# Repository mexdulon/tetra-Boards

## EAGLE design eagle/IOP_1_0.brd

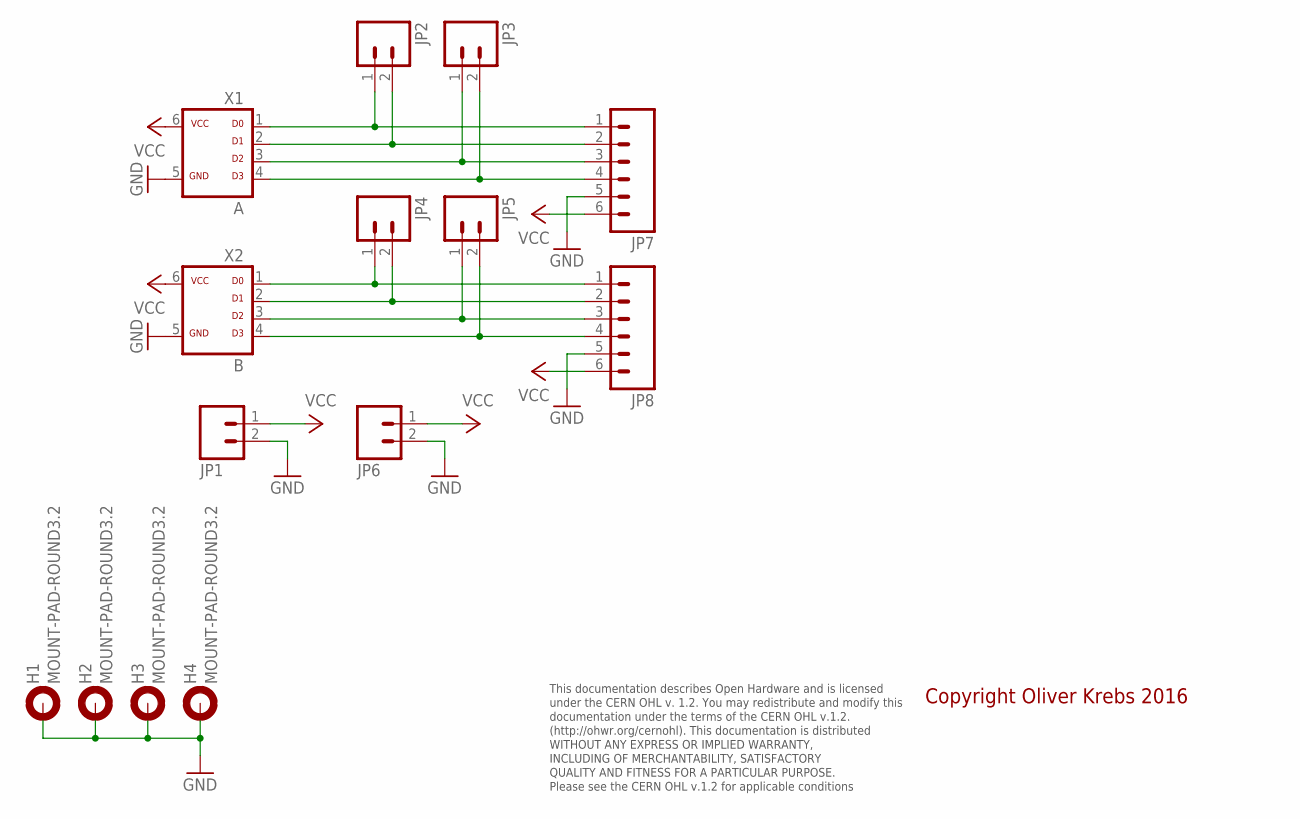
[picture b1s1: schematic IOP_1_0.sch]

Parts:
H1, H2, H3, H4: MOUNT-PAD-ROUND3.2; 3,2-PAD
JP1, JP2, JP3, JP4, JP5, JP6: M021.3MM-5.08; 1X02_BIG_5.08
JP7, JP8: M06SILK_FEMALE_PTH; 1X06
X1: A; ML-6
X2: B; ML-6

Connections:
GND: H1.B3,2, H2.B3,2, H3.B3,2, H4.B3,2, JP1.2, JP6.2, JP7.5, JP8.5, X1.5, X2.5
unnamed: JP2.2, JP7.2, X1.2
unnamed: JP2.1, JP7.1, X1.1
unnamed: JP3.1, JP7.3, X1.3
unnamed: JP3.2, JP7.4, X1.4
unnamed: JP4.1, JP8.1, X2.1
unnamed: JP4.2, JP8.2, X2.2
unnamed: JP5.1, JP8.3, X2.3
unnamed: JP5.2, JP8.4, X2.4
VCC: JP1.1, JP6.1, JP7.6, JP8.6, X1.6, X2.6

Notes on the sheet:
This documentation describes Open Hardware and is licensed under the CERN OHL v. 1.2. You may redistribute and modify this documentation under the terms of the CERN OHL v.1.2. (http://ohwr.org/cernohl). This documentation is distributed WITHOUT ANY EXPRESS OR IMPLIED WARRANTY, INCLUDING OF MERCHANT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
Copyright Oliver Krebs 2016

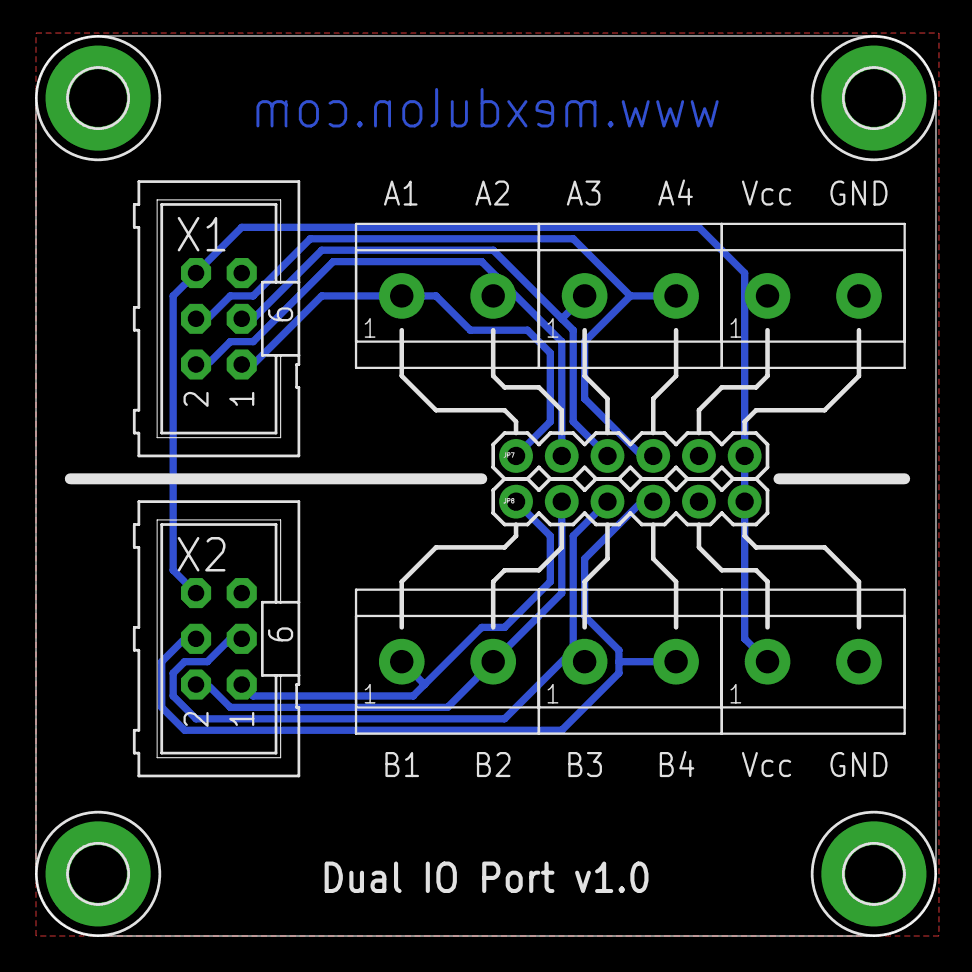
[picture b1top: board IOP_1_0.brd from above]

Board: 2 copper layers, 50.0 x 50.0 mm, 14 parts (0 on the bottom side), 10 nets.

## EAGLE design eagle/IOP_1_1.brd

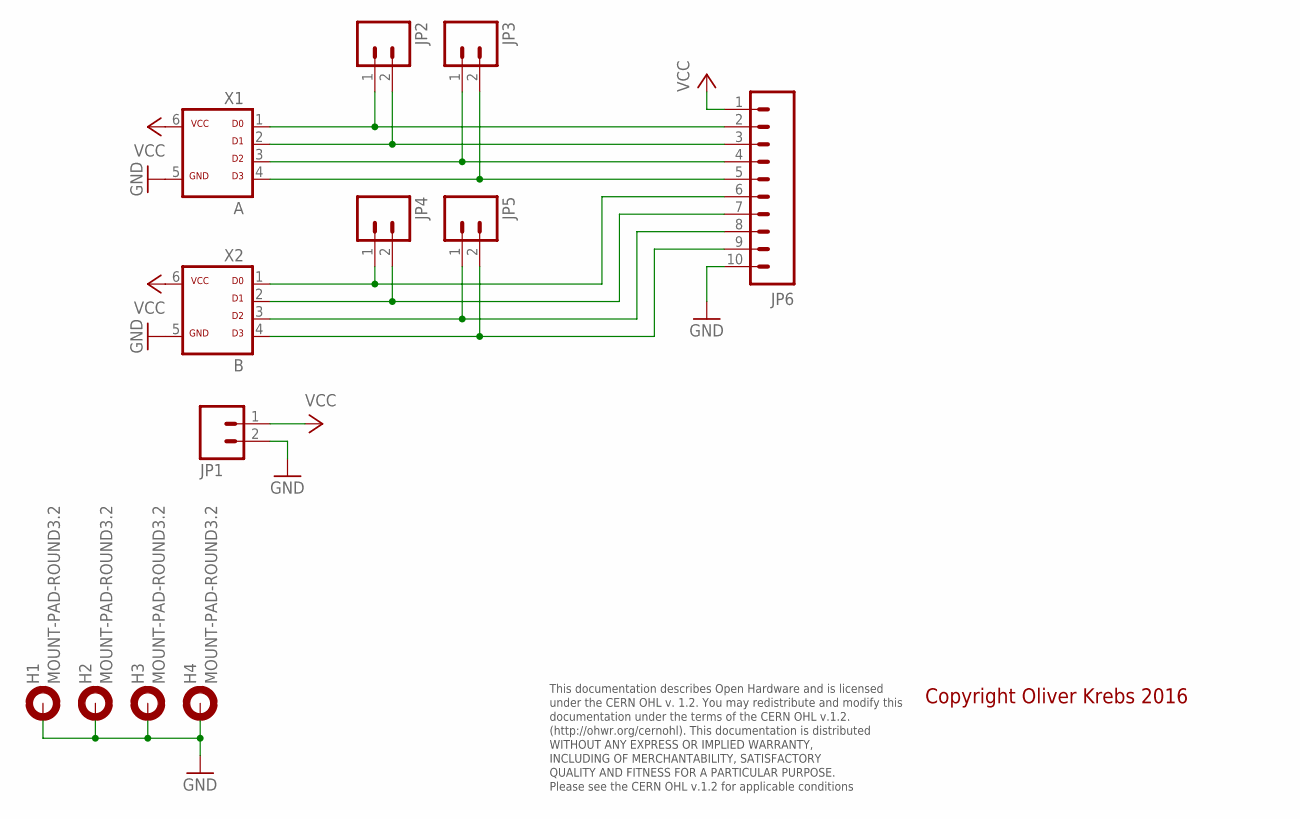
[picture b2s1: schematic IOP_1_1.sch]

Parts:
H1, H2, H3, H4: MOUNT-PAD-ROUND3.2; 3,2-PAD
JP1, JP2, JP3, JP4, JP5: M021.3MM-5.08; 1X02_BIG_5.08
JP6: M10SILK_FEMALE_PTH; 1X10
X1: A; ML-6
X2: B; ML-6

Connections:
GND: H1.B3,2, H2.B3,2, H3.B3,2, H4.B3,2, JP1.2, JP6.10, X1.5, X2.5
unnamed: JP2.2, JP6.3, X1.2
unnamed: JP2.1, JP6.2, X1.1
unnamed: JP3.1, JP6.4, X1.3
unnamed: JP3.2, JP6.5, X1.4
unnamed: JP4.1, JP6.6, X2.1
unnamed: JP4.2, JP6.7, X2.2
unnamed: JP5.1, JP6.8, X2.3
unnamed: JP5.2, JP6.9, X2.4
VCC: JP1.1, JP6.1, X1.6, X2.6

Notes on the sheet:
This documentation describes Open Hardware and is licensed under the CERN OHL v. 1.2. You may redistribute and modify this documentation under the terms of the CERN OHL v.1.2. (http://ohwr.org/cernohl). This documentation is distributed WITHOUT ANY EXPRESS OR IMPLIED WARRANTY, INCLUDING OF MERCHANT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
Copyright Oliver Krebs 2016

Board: 2 copper layers, 12 parts (0 on the bottom side), 10 nets, no tracks yet.

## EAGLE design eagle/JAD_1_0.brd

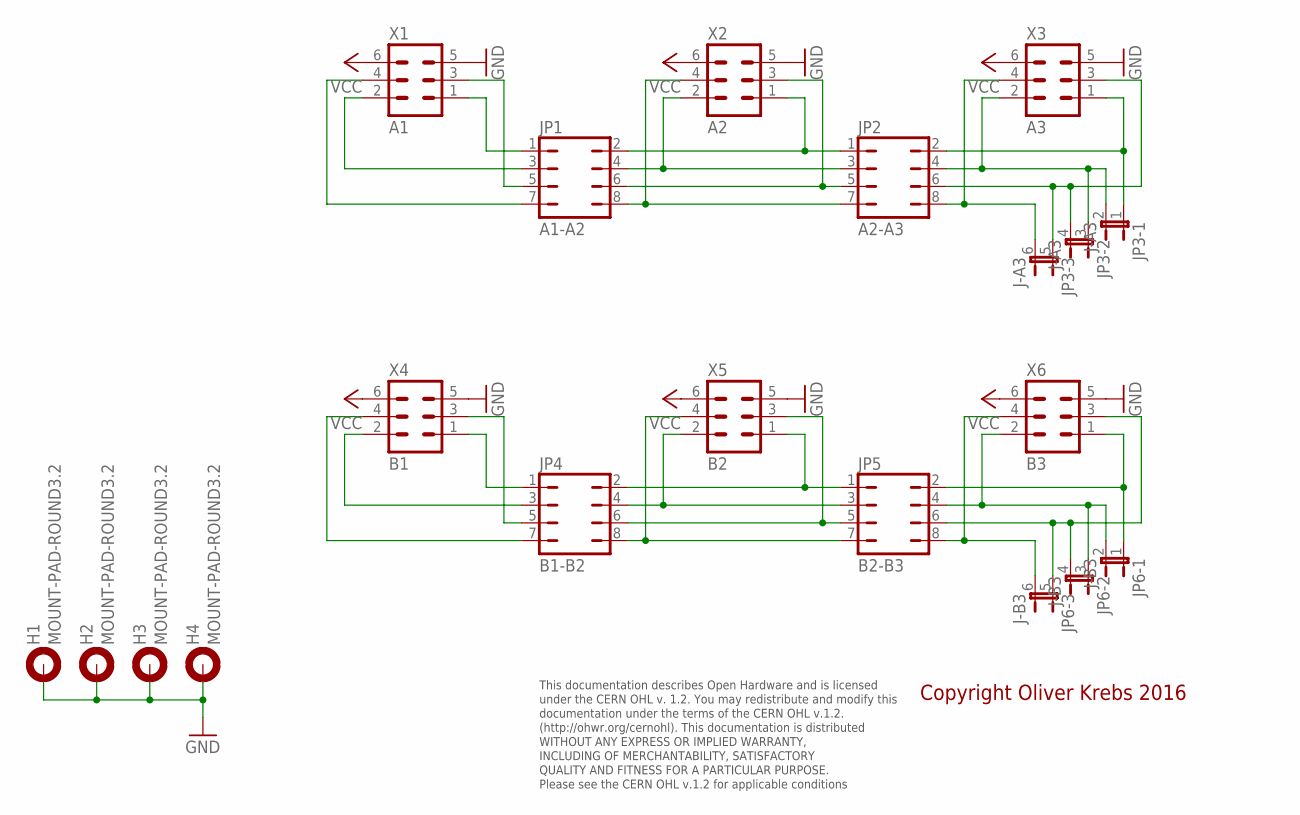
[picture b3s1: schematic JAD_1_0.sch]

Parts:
H1, H2, H3, H4: MOUNT-PAD-ROUND3.2; 3,2-PAD
JP1: A1-A2; JP4Q
JP2: A2-A3; JP4Q
JP3: J-A3; JP3Q
JP4: B1-B2; JP4Q
JP5: B2-B3; JP4Q
JP6: J-B3; JP3Q
X1: A1; ML-6
X2: A2; ML-6
X3: A3; ML-6
X4: B1; ML-6
X5: B2; ML-6
X6: B3; ML-6

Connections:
GND: H1.B3,2, H2.B3,2, H3.B3,2, H4.B3,2, X1.5, X2.5, X3.5, X4.5, X5.5, X6.5
unnamed: JP1.1, X1.1
unnamed: JP1.3, X1.2
unnamed: JP1.5, X1.3
unnamed: JP1.7, X1.4
unnamed: JP1.2, JP2.1, X2.1
unnamed: JP1.4, JP2.3, X2.2
unnamed: JP1.6, JP2.5, X2.3
unnamed: JP1.8, JP2.7, X2.4
unnamed: JP2.2, JP3.1, X3.1
unnamed: JP2.4, JP3.2, JP3.3 (1), X3.2
unnamed: JP2.6, JP3.4 (2), JP3.5 (1), X3.3
unnamed: JP2.8, JP3.6 (2), X3.4
unnamed: JP4.1, X4.1
unnamed: JP4.3, X4.2
unnamed: JP4.5, X4.3
unnamed: JP4.7, X4.4
unnamed: JP4.2, JP5.1, X5.1
unnamed: JP4.4, JP5.3, X5.2
unnamed: JP4.6, JP5.5, X5.3
unnamed: JP4.8, JP5.7, X5.4
unnamed: JP5.2, JP6.1, X6.1
unnamed: JP5.4, JP6.2, JP6.3 (1), X6.2
unnamed: JP5.6, JP6.4 (2), JP6.5 (1), X6.3
unnamed: JP5.8, JP6.6 (2), X6.4
VCC: X1.6, X2.6, X3.6, X4.6, X5.6, X6.6

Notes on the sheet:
This documentation describes Open Hardware and is licensed under the CERN OHL v. 1.2. You may redistribute and modify this documentation under the terms of the CERN OHL v.1.2. (http://ohwr.org/cernohl). This documentation is distributed WITHOUT ANY EXPRESS OR IMPLIED WARRANTY, INCLUDING OF MERCHANT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
Copyright Oliver Krebs 2016

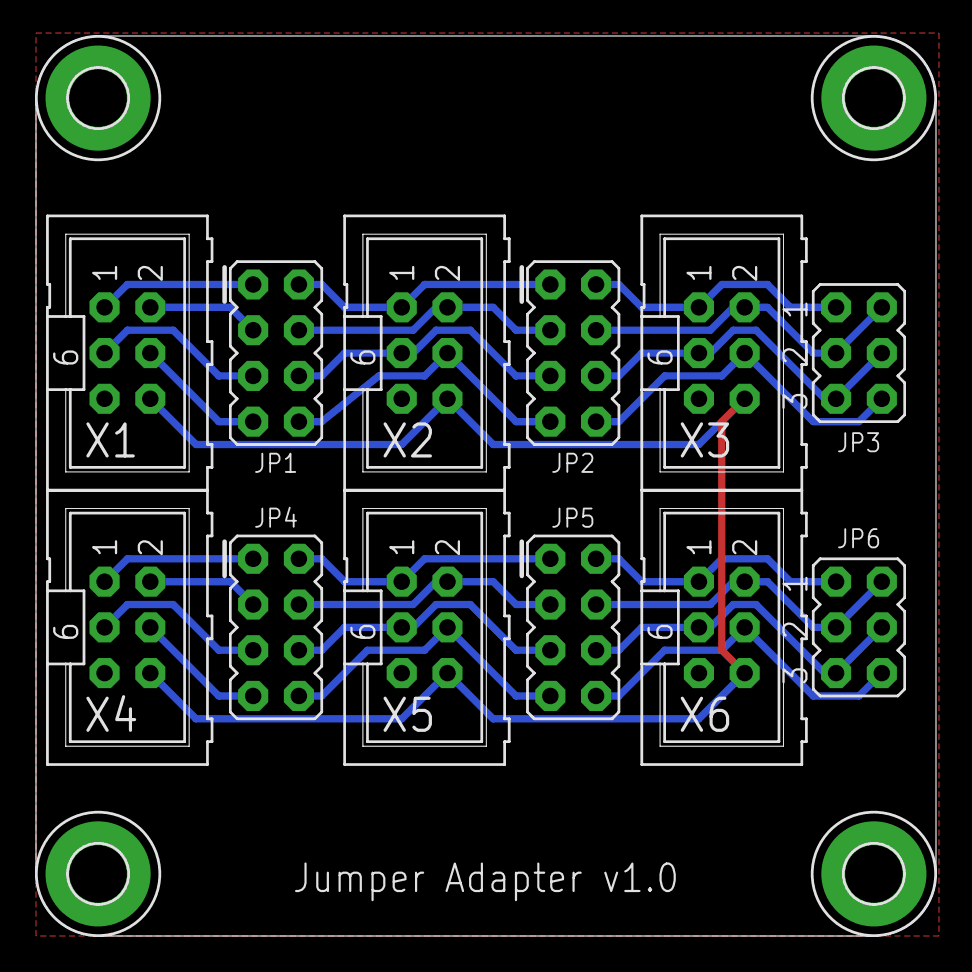
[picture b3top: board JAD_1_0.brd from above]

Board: 2 copper layers, 50.0 x 50.0 mm, 16 parts (0 on the bottom side), 26 nets.

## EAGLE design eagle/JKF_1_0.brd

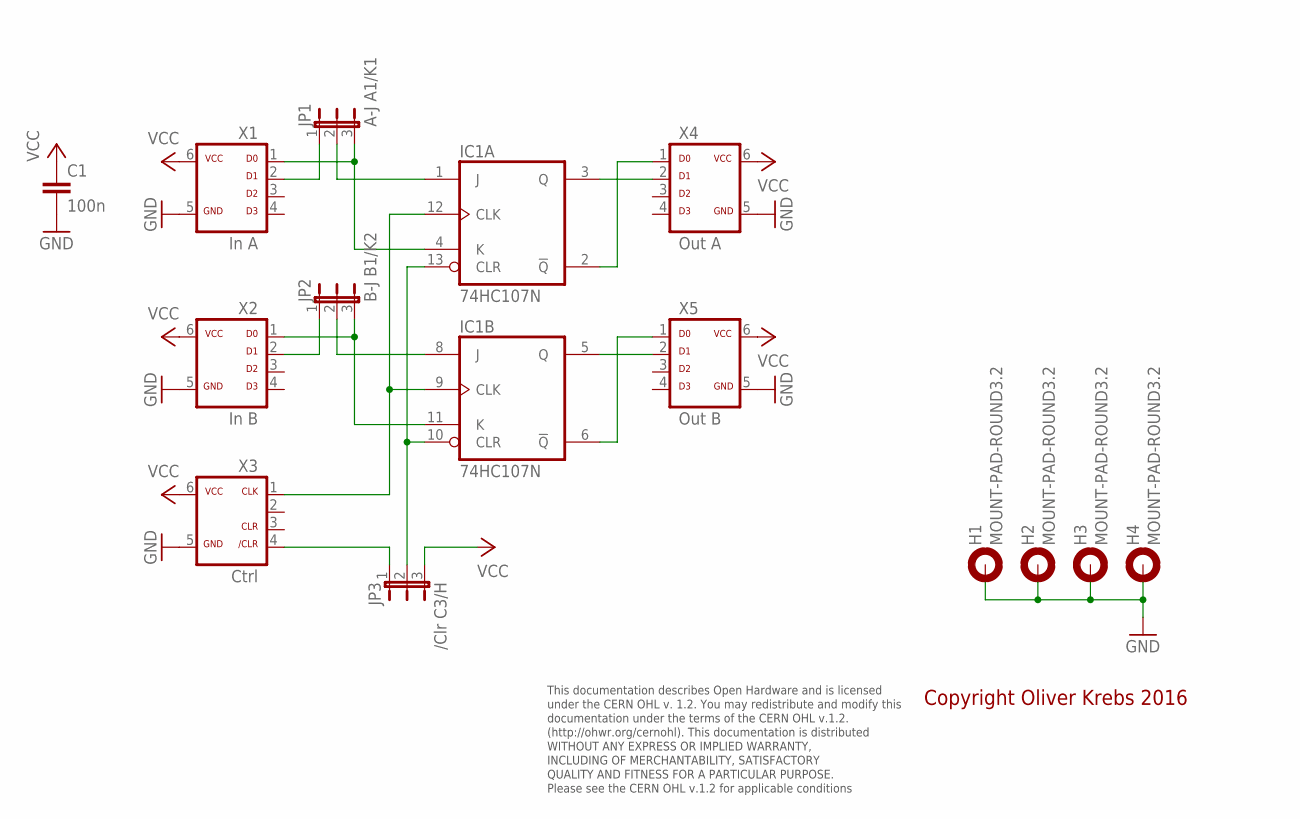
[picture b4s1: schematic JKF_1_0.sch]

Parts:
C1: 100n; C050-025X075
H1, H2, H3, H4: MOUNT-PAD-ROUND3.2; 3,2-PAD
IC1: 74HC107N; DIL14
JP1: A-J A1/K1; JP2
JP2: B-J B1/K2; JP2
JP3: /Clr C3/H; JP2
X1: In A; ML-6
X2: In B; ML-6
X3: Ctrl; ML-6
X4: Out A; ML-6
X5: Out B; ML-6

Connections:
GND: C1.2, H1.B3,2, H2.B3,2, H3.B3,2, H4.B3,2, IC1.7 (GND), X1.5, X2.5, X3.5, X4.5, X5.5
unnamed: IC1.4 (K), JP1.3, X1.1
unnamed: JP3.1, X3.4
unnamed: IC1.9 (CLK), IC1.12 (CLK), X3.1
unnamed: IC1.10 (CLR), IC1.13 (CLR), JP3.2
unnamed: IC1.11 (K), JP2.3, X2.1
unnamed: IC1.2 (!Q), X4.1
unnamed: IC1.3 (Q), X4.2
unnamed: IC1.6 (!Q), X5.1
unnamed: IC1.5 (Q), X5.2
unnamed: IC1.8 (J), JP2.2
unnamed: IC1.1 (J), JP1.2
unnamed: JP2.1, X2.2
unnamed: JP1.1, X1.2
VCC: C1.1, IC1.14 (VCC), JP3.3, X1.6, X2.6, X3.6, X4.6, X5.6

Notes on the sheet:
This documentation describes Open Hardware and is licensed under the CERN OHL v. 1.2. You may redistribute and modify this documentation under the terms of the CERN OHL v.1.2. (http://ohwr.org/cernohl). This documentation is distributed WITHOUT ANY EXPRESS OR IMPLIED WARRANTY, INCLUDING OF MERCHANT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
Copyright Oliver Krebs 2016

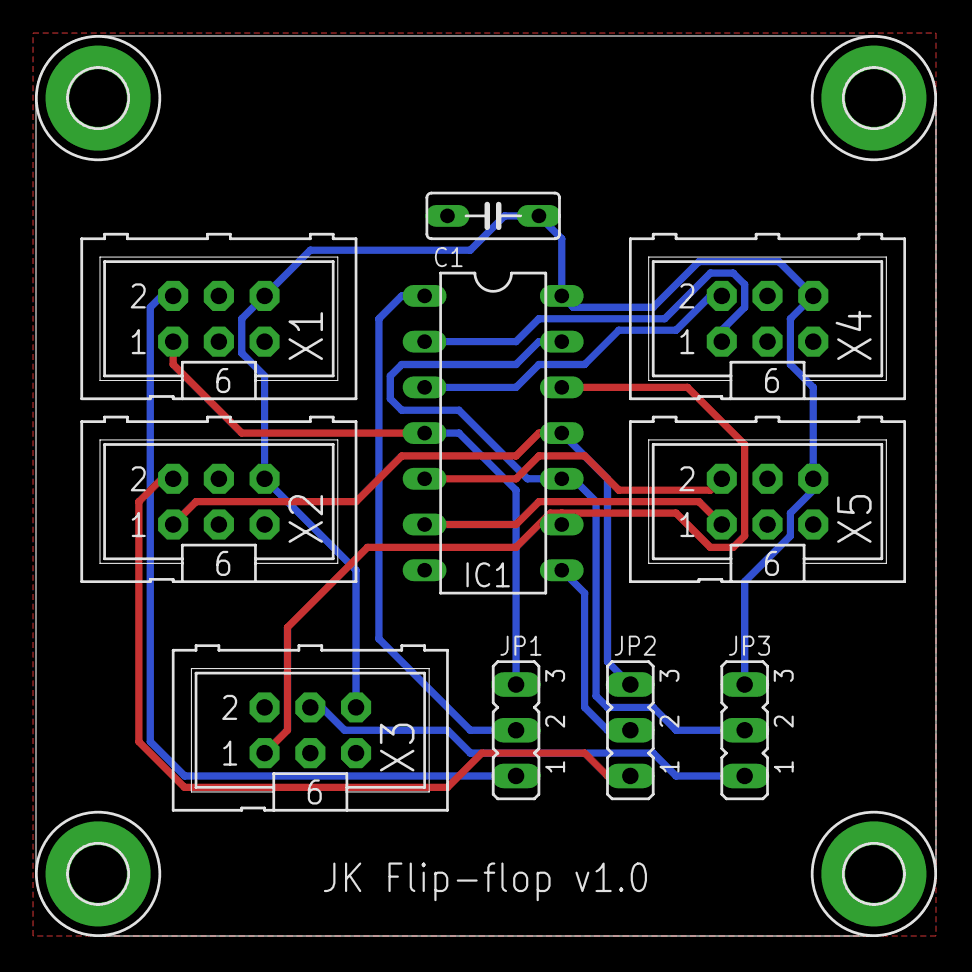
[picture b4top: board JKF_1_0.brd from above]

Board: 2 copper layers, 50.0 x 50.0 mm, 14 parts (0 on the bottom side), 15 nets.

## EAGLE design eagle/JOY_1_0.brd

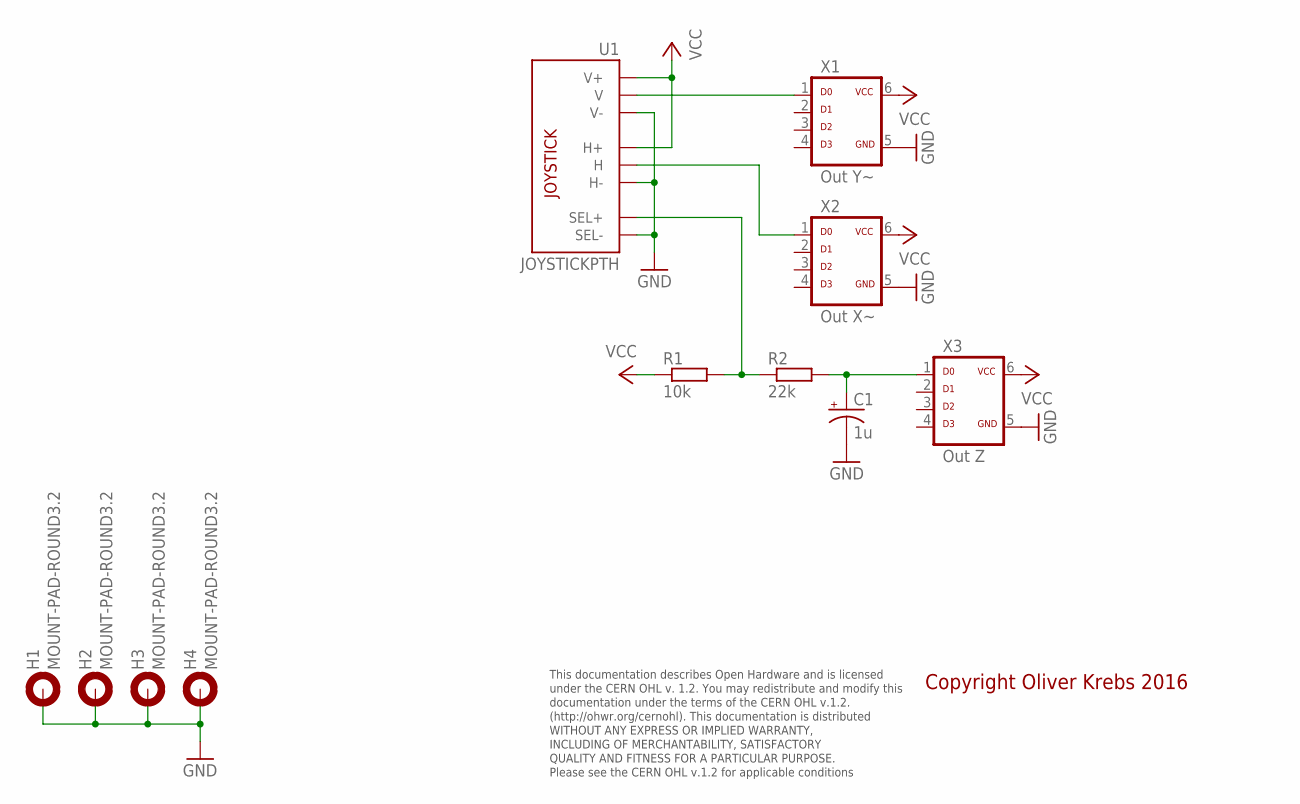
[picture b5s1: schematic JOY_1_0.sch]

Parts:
C1: 1u; CPOL-RADIAL-10UF-25V
H1, H2, H3, H4: MOUNT-PAD-ROUND3.2; 3,2-PAD
R1: 10k; 0207/10
R2: 22k; 0207/10
U1: JOYSTICKPTH; JOYSTICK
X1: Out Y~; ML-6
X2: Out X~; ML-6
X3: Out Z; ML-6

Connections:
GND: C1.2 (-), H1.B3,2, H2.B3,2, H3.B3,2, H4.B3,2, U1.B2A (SEL-), U1.H3 (H-), U1.V3 (V-), X1.5, X2.5, X3.5
unnamed: U1.V2 (V), X1.1
unnamed: U1.H2 (H), X2.1
unnamed: R1.2, R2.1, U1.B1A (SEL+)
unnamed: C1.1 (+), R2.2, X3.1
VCC: R1.1, U1.H1 (H+), U1.V1 (V+), X1.6, X2.6, X3.6

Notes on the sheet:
This documentation describes Open Hardware and is licensed under the CERN OHL v. 1.2. You may redistribute and modify this documentation under the terms of the CERN OHL v.1.2. (http://ohwr.org/cernohl). This documentation is distributed WITHOUT ANY EXPRESS OR IMPLIED WARRANTY, INCLUDING OF MERCHANT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
Copyright Oliver Krebs 2016

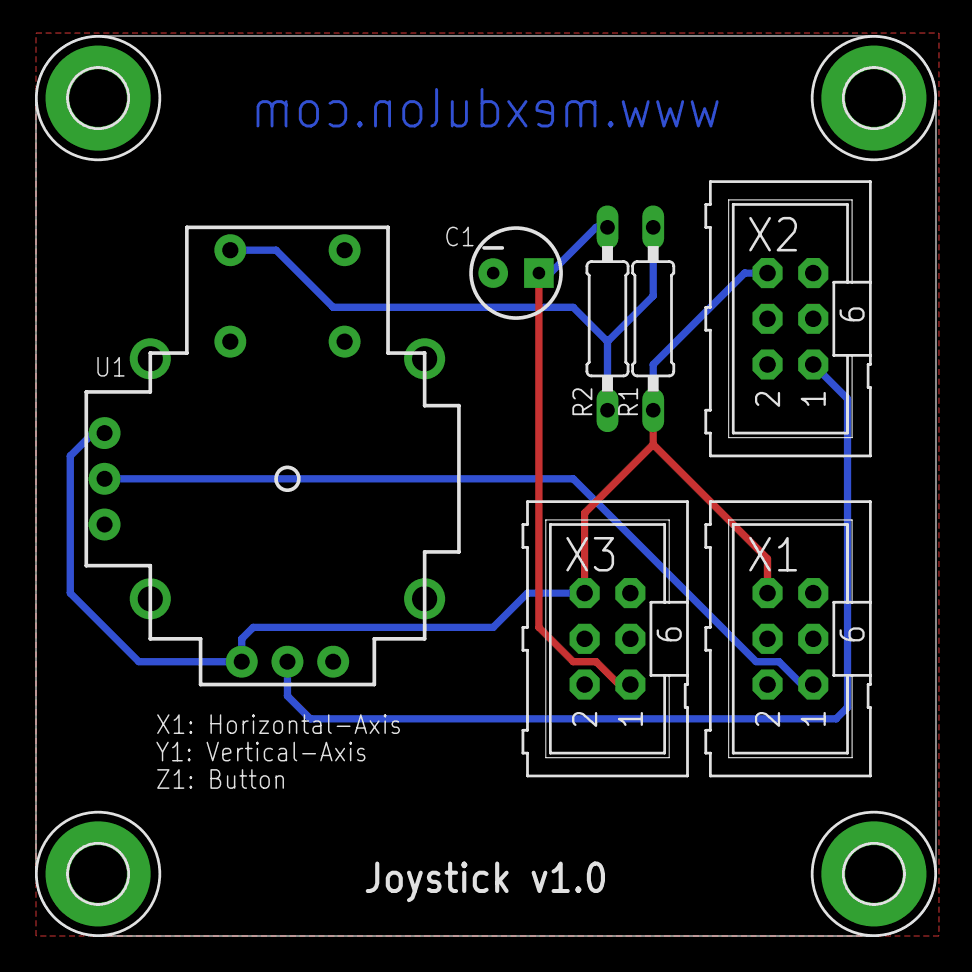
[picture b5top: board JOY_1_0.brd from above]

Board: 2 copper layers, 50.0 x 50.0 mm, 11 parts (0 on the bottom side), 6 nets.

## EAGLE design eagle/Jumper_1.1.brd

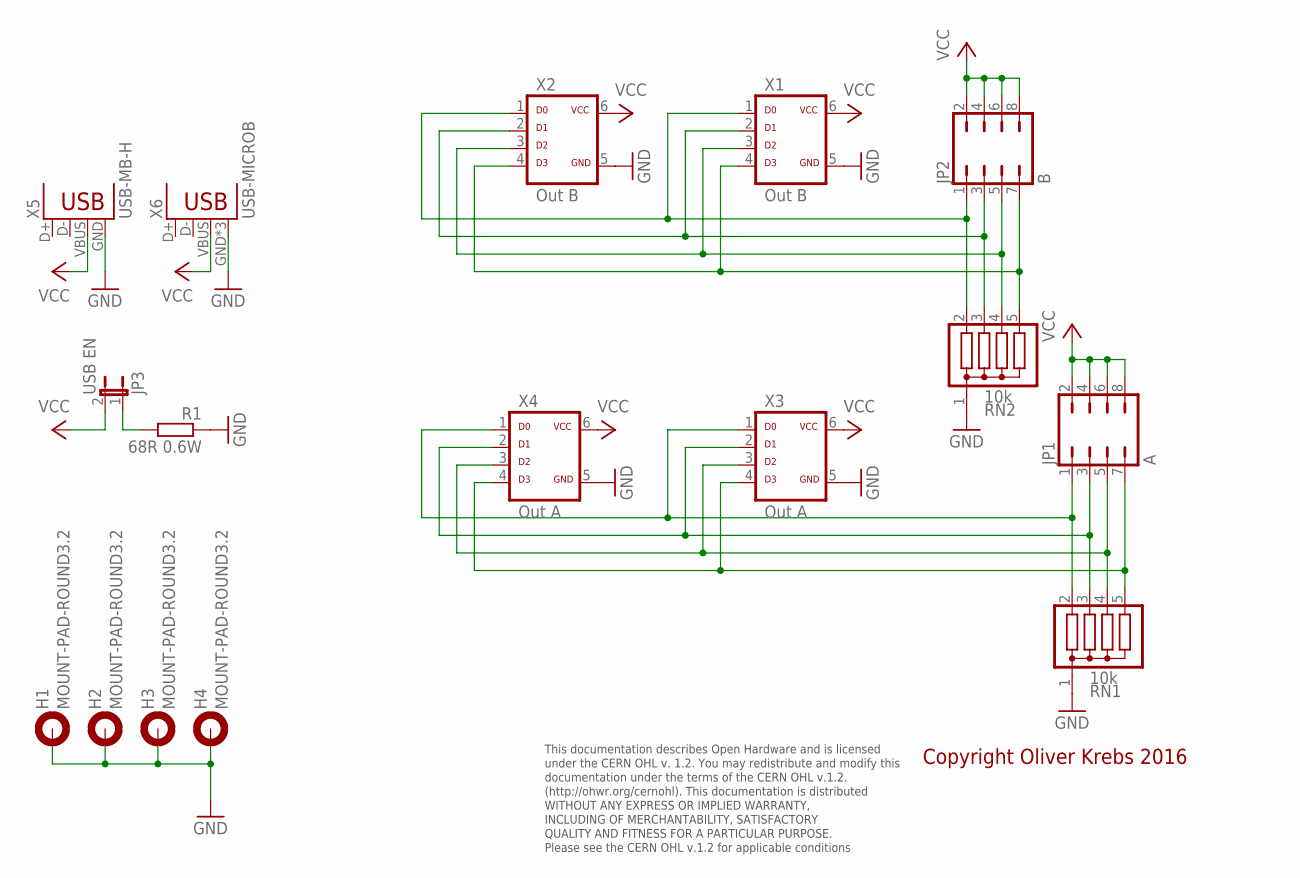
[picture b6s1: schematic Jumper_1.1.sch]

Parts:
H1, H2, H3, H4: MOUNT-PAD-ROUND3.2; 3,2-PAD
JP1: A; JP4Q
JP2: B; JP4Q
JP3: USB EN; JP1
R1: 68R 0.6W; 0207/10
RN1, RN2: 10k; SIL5
X1, X2: Out B; ML-6
X3, X4: Out A; ML-6
X5: USB-MB-H
X6: USB-MICROB

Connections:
GND: H1.B3,2, H2.B3,2, H3.B3,2, H4.B3,2, R1.1, RN1.1, RN2.1, X1.5, X2.5, X3.5, X4.5, X5.GND, X6.GND, X6.MT1 (GND), X6.MT2 (GND)
unnamed: JP2.1, RN2.2, X1.1, X2.1
unnamed: JP2.3, RN2.3, X1.2, X2.2
unnamed: JP1.1, RN1.2, X3.1, X4.1
unnamed: JP2.7, RN2.5, X1.4, X2.4
unnamed: JP1.3, RN1.3, X3.2, X4.2
unnamed: JP1.7, RN1.5, X3.4, X4.4
unnamed: JP2.5, RN2.4, X1.3, X2.3
unnamed: JP1.5, RN1.4, X3.3, X4.3
unnamed: JP3.1, R1.2
VCC: JP1.2, JP1.4, JP1.6, JP1.8, JP2.2, JP2.4, JP2.6, JP2.8, JP3.2, X1.6, X2.6, X3.6, X4.6, X5.VBUS, X6.VBUS

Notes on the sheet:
This documentation describes Open Hardware and is licensed under the CERN OHL v. 1.2. You may redistribute and modify this documentation under the terms of the CERN OHL v.1.2. (http://ohwr.org/cernohl). This documentation is distributed WITHOUT ANY EXPRESS OR IMPLIED WARRANTY, INCLUDING OF MERCHANT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
Copyright Oliver Krebs 2016

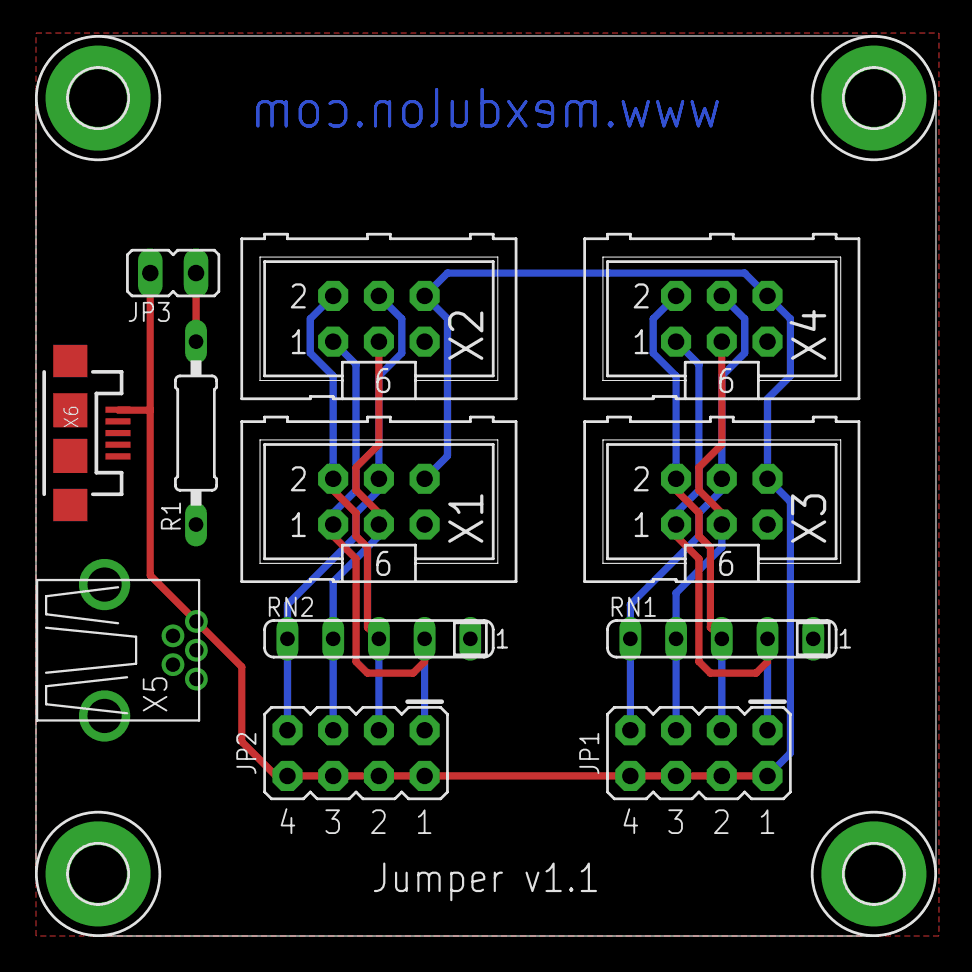
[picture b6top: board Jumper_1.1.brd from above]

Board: 2 copper layers, 50.0 x 50.0 mm, 16 parts (0 on the bottom side), 11 nets.

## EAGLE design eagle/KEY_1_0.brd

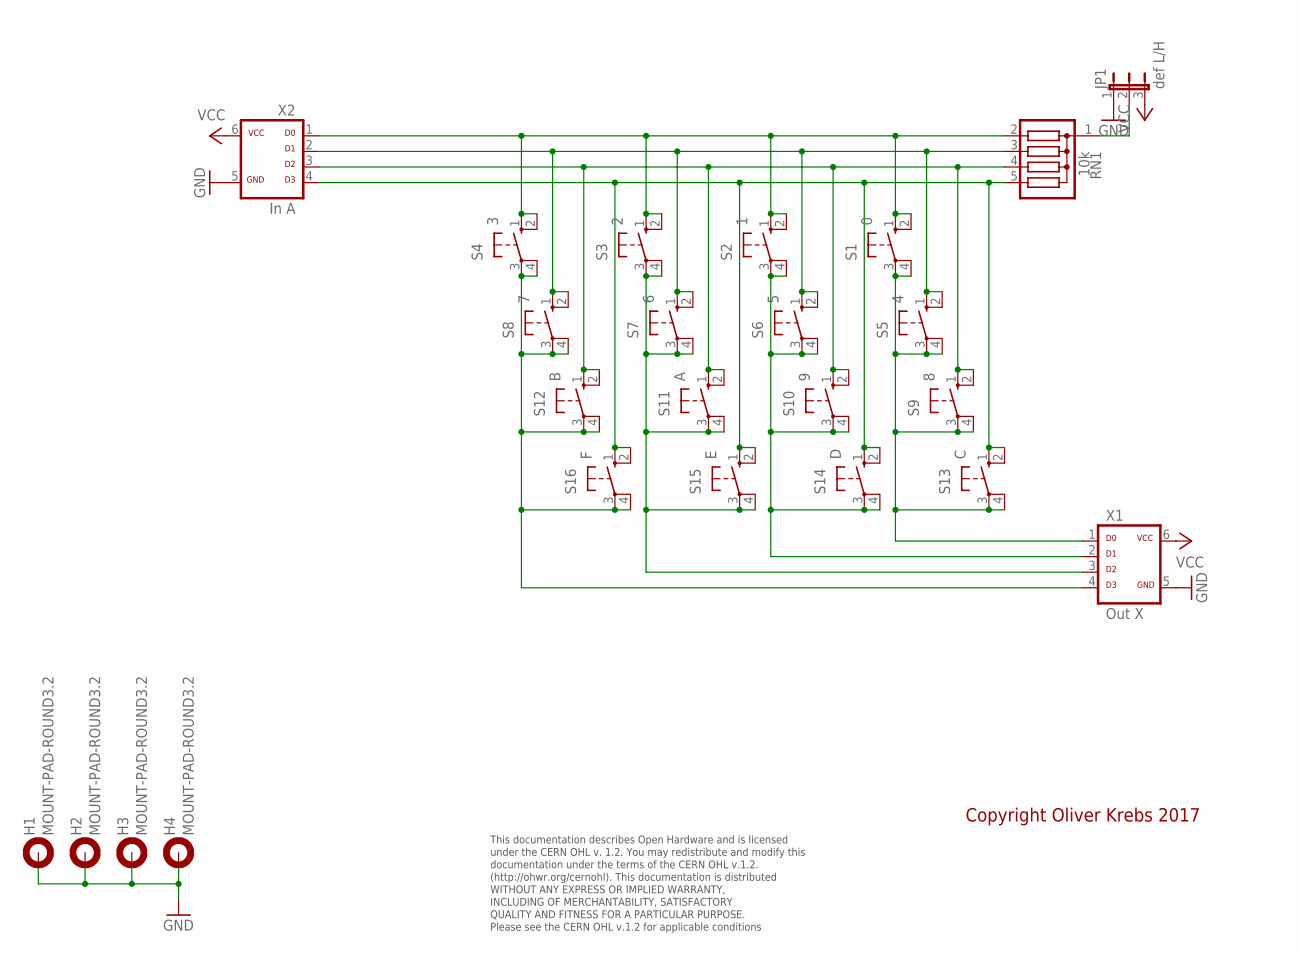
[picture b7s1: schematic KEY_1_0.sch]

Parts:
H1, H2, H3, H4: MOUNT-PAD-ROUND3.2; 3,2-PAD
JP1: def L/H; JP2-U
RN1: 10k; SIL5
S1: 0; B3F-10XX
S2: 1; B3F-10XX
S3: 2; B3F-10XX
S4: 3; B3F-10XX
S5: 4; B3F-10XX
S6: 5; B3F-10XX
S7: 6; B3F-10XX
S8: 7; B3F-10XX
S9: 8; B3F-10XX
S10: 9; B3F-10XX
S11: A; B3F-10XX
S12: B; B3F-10XX
S13: C; B3F-10XX
S14: D; B3F-10XX
S15: E; B3F-10XX
S16: F; B3F-10XX
X1: Out X; ML-6
X2: In A; ML-6

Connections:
GND: H1.B3,2, H2.B3,2, H3.B3,2, H4.B3,2, JP1.1, X1.5, X2.5
unnamed: JP1.2, RN1.1
unnamed: RN1.4, S9.1 (S), S9.2 (S1), S10.1 (S), S10.2 (S1), S11.1 (S), S11.2 (S1), S12.1 (S), S12.2 (S1), X2.3
unnamed: RN1.5, S13.1 (S), S13.2 (S1), S14.1 (S), S14.2 (S1), S15.1 (S), S15.2 (S1), S16.1 (S), S16.2 (S1), X2.4
unnamed: RN1.2, S1.1 (S), S1.2 (S1), S2.1 (S), S2.2 (S1), S3.1 (S), S3.2 (S1), S4.1 (S), S4.2 (S1), X2.1
unnamed: RN1.3, S5.1 (S), S5.2 (S1), S6.1 (S), S6.2 (S1), S7.1 (S), S7.2 (S1), S8.1 (S), S8.2 (S1), X2.2
unnamed: S2.3, S2.4 (P1), S6.3, S6.4 (P1), S10.3, S10.4 (P1), S14.3, S14.4 (P1), X1.2
unnamed: S1.3, S1.4 (P1), S5.3, S5.4 (P1), S9.3, S9.4 (P1), S13.3, S13.4 (P1), X1.1
unnamed: S4.3, S4.4 (P1), S8.3, S8.4 (P1), S12.3, S12.4 (P1), S16.3, S16.4 (P1), X1.4
unnamed: S3.3, S3.4 (P1), S7.3, S7.4 (P1), S11.3, S11.4 (P1), S15.3, S15.4 (P1), X1.3
VCC: JP1.3, X1.6, X2.6

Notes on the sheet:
This documentation describes Open Hardware and is licensed under the CERN OHL v. 1.2. You may redistribute and modify this documentation under the terms of the CERN OHL v.1.2. (http://ohwr.org/cernohl). This documentation is distributed WITHOUT ANY EXPRESS OR IMPLIED WARRANTY, INCLUDING OF MERCHANT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
Copyright Oliver Krebs 2017

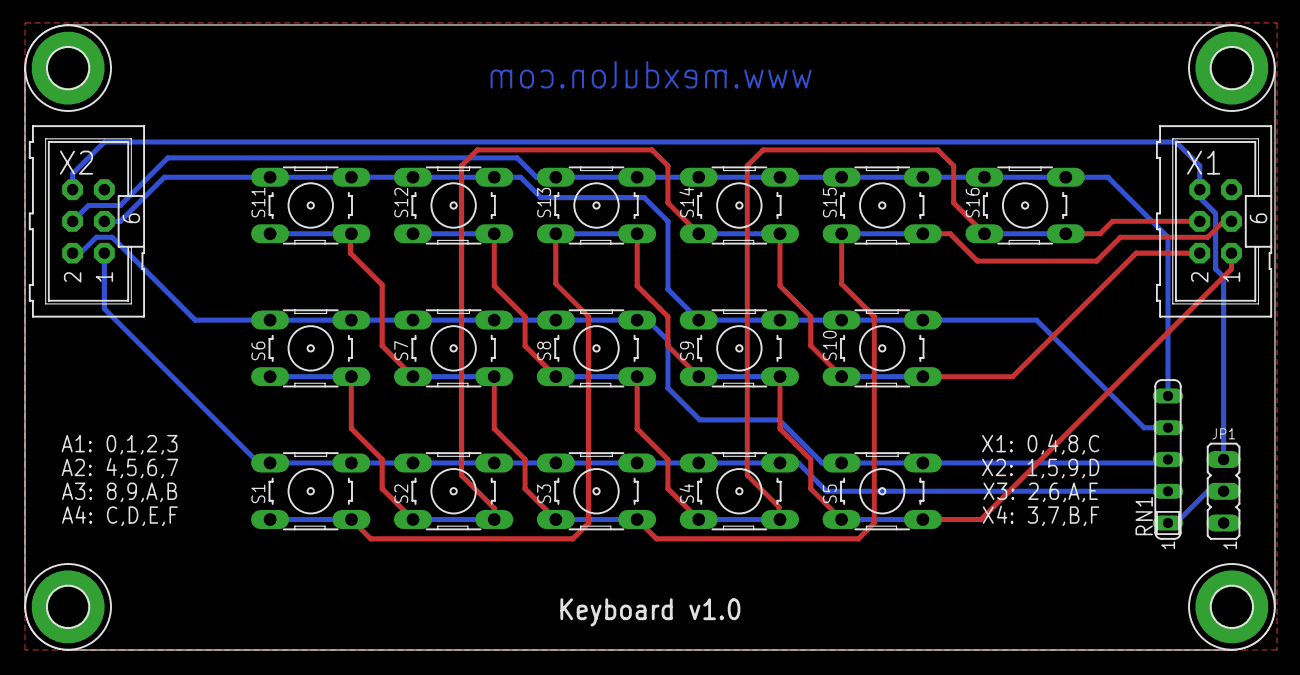
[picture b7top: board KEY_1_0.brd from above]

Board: 2 copper layers, 100.0 x 50.0 mm, 24 parts (0 on the bottom side), 11 nets.

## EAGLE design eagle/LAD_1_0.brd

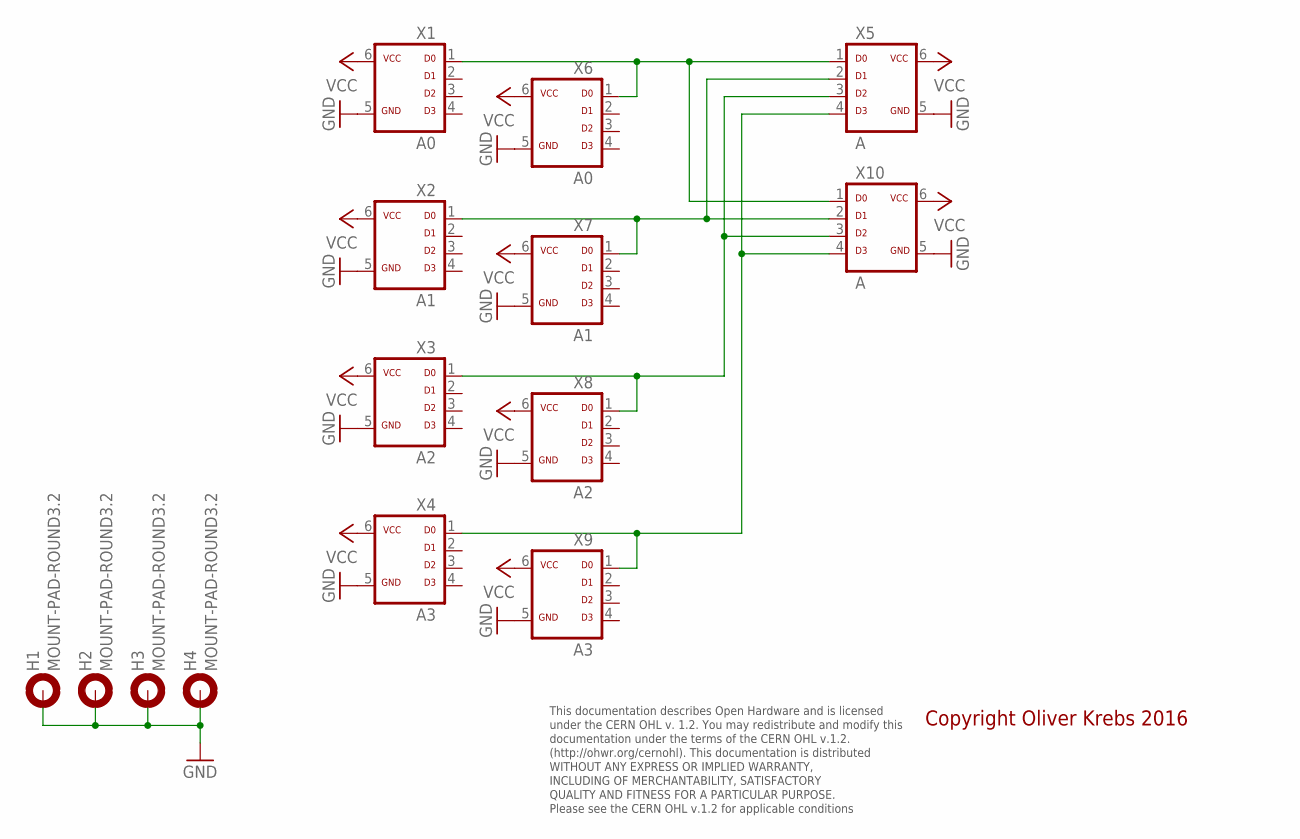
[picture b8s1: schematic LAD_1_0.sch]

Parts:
H1, H2, H3, H4: MOUNT-PAD-ROUND3.2; 3,2-PAD
X1, X6: A0; ML-6
X2, X7: A1; ML-6
X3, X8: A2; ML-6
X4, X9: A3; ML-6
X5, X10: A; ML-6

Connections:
GND: H1.B3,2, H2.B3,2, H3.B3,2, H4.B3,2, X1.5, X2.5, X3.5, X4.5, X5.5, X6.5, X7.5, X8.5, X9.5, X10.5
unnamed: X4.1, X5.4, X9.1, X10.4
unnamed: X3.1, X5.3, X8.1, X10.3
unnamed: X2.1, X5.2, X7.1, X10.2
unnamed: X1.1, X5.1, X6.1, X10.1
VCC: X1.6, X2.6, X3.6, X4.6, X5.6, X6.6, X7.6, X8.6, X9.6, X10.6

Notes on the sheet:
This documentation describes Open Hardware and is licensed under the CERN OHL v. 1.2. You may redistribute and modify this documentation under the terms of the CERN OHL v.1.2. (http://ohwr.org/cernohl). This documentation is distributed WITHOUT ANY EXPRESS OR IMPLIED WARRANTY, INCLUDING OF MERCHANT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
Copyright Oliver Krebs 2016

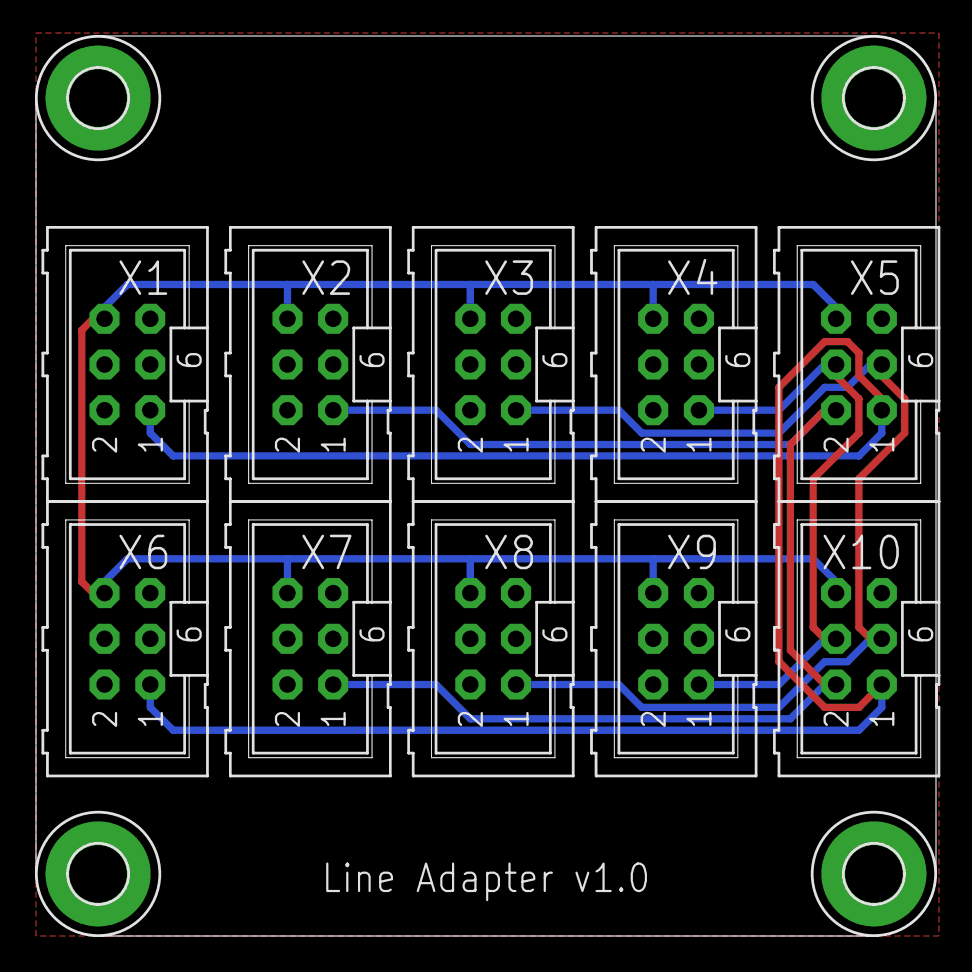
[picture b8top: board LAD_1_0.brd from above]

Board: 2 copper layers, 50.0 x 50.0 mm, 14 parts (0 on the bottom side), 6 nets.

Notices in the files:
eagle/IOP_1_0.brd:
Licensed under CERN OHL v.1.2
parts and their libraries:
SparkFun-Connectors: Licensing: Creative Commons ShareAlike 4.0 International - https://creativecommons.org/licenses/by-sa/4.0
